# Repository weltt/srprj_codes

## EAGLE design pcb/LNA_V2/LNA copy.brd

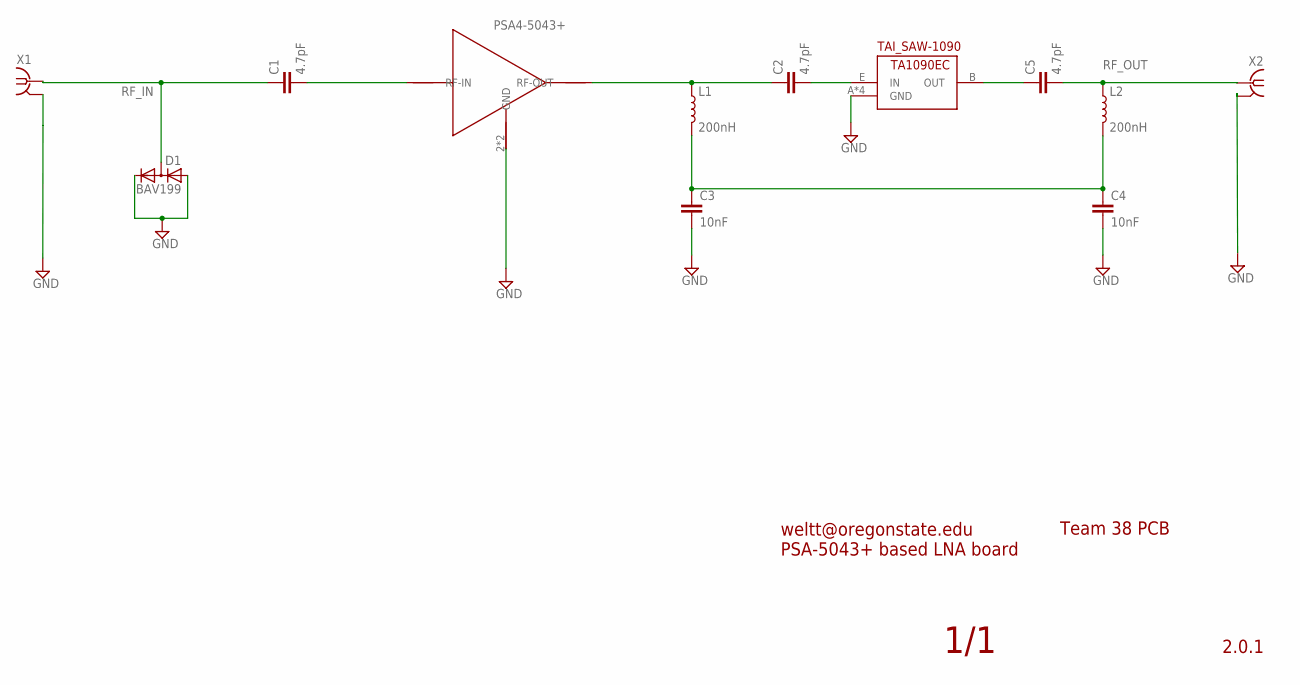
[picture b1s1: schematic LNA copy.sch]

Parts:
C1, C2, C5: 4.7pF; C0402
C3, C4: 10nF; C0402
D1: BAV199; SOT23
L1, L2: 200nH; 0603
PSA$-5043: PSA4-5043+
U$1: TA1090EC
X1, X2: SMA-142-0701-801/806; J502-ND-142-0701-801/806

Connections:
BIAS_TEE: C3.1, C4.1, L1.2, L2.2
FIN: C2.2, U$1.E (IN)
GND: C3.2, C4.2, D1.1 (A), D1.2 (C), PSA$-5043.2 (GND), PSA$-5043.4 (GND), U$1.A (GND), U$1.C (GND), U$1.D (GND), U$1.F (GND), X1.G@1 (2), X1.G@2 (2), X1.G@3 (2), X1.G@4 (2), X2.G@1 (2), X2.G@2 (2), X2.G@3 (2), X2.G@4 (2)
LNA_OUT: C2.1, L1.1, PSA$-5043.1 (RF-OUT)
unnamed: C1.2, PSA$-5043.3 (RF-IN)
unnamed: C5.1, U$1.B (OUT)
RF_IN: C1.1, D1.3 (AC), X1.1
RF_OUT: C5.2, L2.1, X2.1

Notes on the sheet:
Team 38 PCB
weltt@oregonstate.edu PSA-5043+ based LNA board
1/1
2.0.1

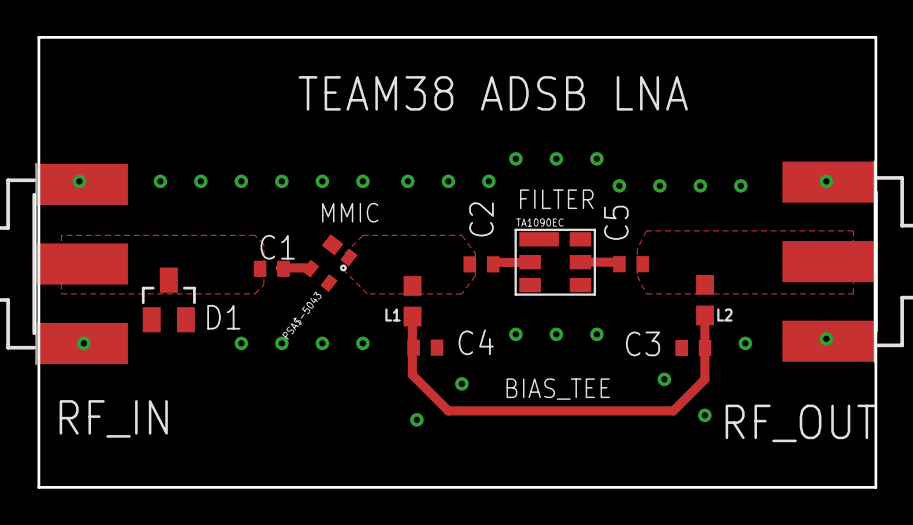
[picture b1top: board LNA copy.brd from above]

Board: 2 copper layers, 46.6 x 25.0 mm, 12 parts (0 on the bottom side), 8 nets.

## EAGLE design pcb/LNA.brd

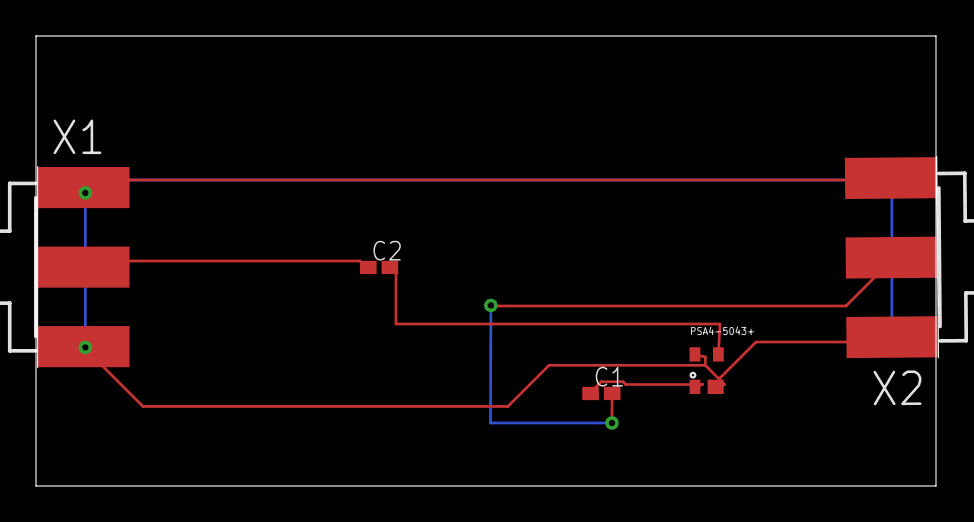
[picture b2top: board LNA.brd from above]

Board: 2 copper layers, 50.1 x 25.0 mm, 5 parts (0 on the bottom side), 5 nets.

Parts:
C1, C2: 100pF; C0402K
PSA4-5043+: PSA4-5043+
X1, X2: SMA-142-0701-801/806; J502-ND-142-0701-801/806

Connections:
GND: PSA4-5043+.2, PSA4-5043+.4, X1.G@1, X1.G@2, X1.G@3, X1.G@4, X2.G@2, X2.G@4
unnamed: C2.2, PSA4-5043+.3
unnamed: C1.1, PSA4-5043+.1
unnamed: C2.1, X1.1
unnamed: C1.2, X2.1

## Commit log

2017-11-12 Adding directories
2018-02-09 Update PCB mostly
2018-03-12 PCB Update
    Update PCB with Filter
2018-03-15 Update of pcb images.
2018-03-15 Updating PCB images
2018-03-15 BOM
    Bill of Materials

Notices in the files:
parts and their libraries:
SparkFun-Coils: Licensing: Creative Commons ShareAlike 4.0 International - https://creativecommons.org/licenses/by-sa/4.0
